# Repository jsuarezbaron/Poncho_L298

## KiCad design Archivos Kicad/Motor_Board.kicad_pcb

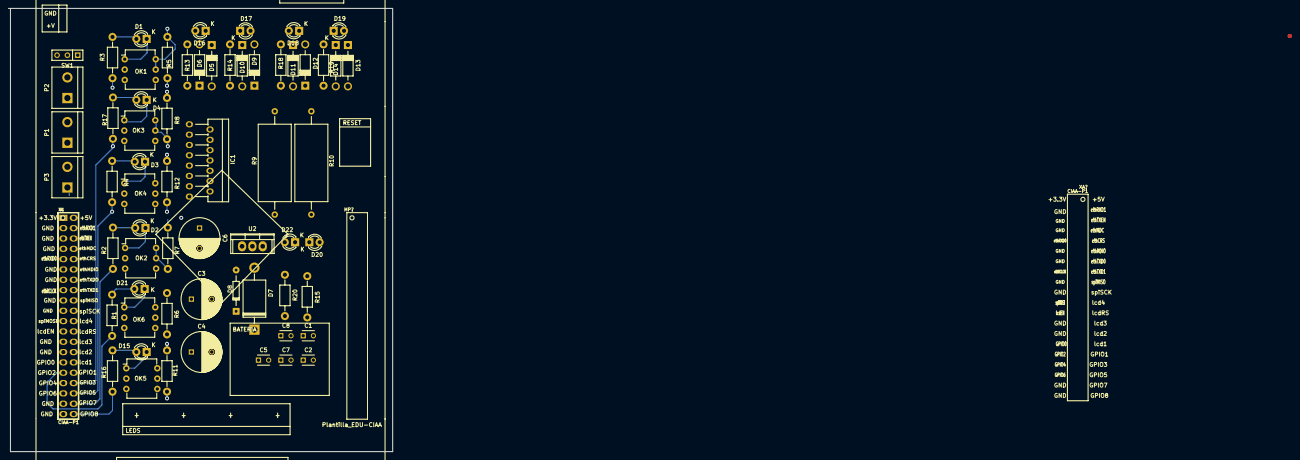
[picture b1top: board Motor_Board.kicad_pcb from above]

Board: 2 copper layers, 94.5 x 109.0 mm, 68 parts (0 on the bottom side), 34 nets.

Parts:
C1, C2, C5, C7, C8: 0.1uF; C_Disc_D3_P2.5
C3, C4: 470uF; C_Radial_D10_L25_P5
C6: 220uF; C_Radial_D10_L16_P5
D1, D2, D3, D4, D15, D16, D17, D18, D19, D20, D21, D22: Led_Small; LED-3MM
D5, D6, D9, D10, D11, D12, D13, D14: 1N4007; Diode_DO-41_SOD81_Horizontal_RM10
D7: 1N5822; Diode_DO-201AD_Horizontal_RM15
D8: 1N4734A; Diode_DO-35_SOD27_Horizontal_RM10
F1, F2, F3: FIDUCIAL; Fiducial_1mm
IC1: L298; Multiwatt_15_Vertical
MP?: Plantilla_EDU-CIAA
OK1, OK2, OK3, OK4, OK5, OK6: 4N35; DIP-6_W7.62mm
P1: Motor A; bornier2
P2: VDD Motor; bornier2
P3: Motor B; bornier2
R1, R2, R3, R4, R15, R16, R17: 330; Resistor_Horizontal_RM10mm
R5, R6, R7, R8, R11, R12, R13, R14, R18, R19, R20: 1K; Resistor_Horizontal_RM10mm
R9, R10: 0.5; Resistor_Ceramic_Horizontal_L19mm-W8mm-H8mm-p25mm
SW1: Switch_SPDT_x2; SW_Micro_SPST
U2: 7805; TO-220
XA1: Conn_Poncho2P_2x_20x2; Conn_Poncho_Izquierda
XA?: Plantilla_Poncho_Izquierda; Plantilla_Poncho_Plantilla_Poncho_Izquierda

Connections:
/ENA: IC1.6, OK6.5, OK6.6, R6.2
/ENB: IC1.11, OK5.5, OK5.6, R11.2
/IN1: IC1.5, OK1.5, OK1.6, R5.1
/IN2: IC1.7, OK2.5, OK2.6, R7.2
/IN3: IC1.10, OK3.5, OK3.6, R8.2
/IN4: IC1.12, OK4.5, OK4.6, R12.2
/OUT1: IC1.2, P1.1, R13.1
/OUT2: IC1.3, P1.2, R14.1
/OUT3: IC1.13, P3.1, R18.1
/OUT4: IC1.14, P3.2, R19.1
GNDA: C1.2, C2.2, C3.2, C4.2, C5.2, C6.2, C7.2, C8.2, D16.1, D17.1, D18.1, D19.1, D20.1, D20.2, D22.1, IC1.8, OK1.4, OK2.4, OK3.4, OK4.4, OK5.4, OK6.4, P2.1, R9.2, R10.2, R15.1
unnamed: D1.1, OK1.1
unnamed: D1.2, R3.1
unnamed: D2.1, OK2.1
unnamed: D2.2, R2.1
unnamed: D3.1, OK4.1
unnamed: D3.2, R4.1
unnamed: D4.1, OK3.1
unnamed: D4.2, R17.1
unnamed: D15.1, OK5.1
unnamed: D15.2, R16.1
unnamed: D16.2, R13.2
unnamed: D17.2, R14.2
unnamed: D18.2, R18.2
unnamed: D19.2, R19.2
unnamed: D21.1, OK6.1
unnamed: D21.2, R1.1
unnamed: D22.2, R20.1
unnamed: IC1.1, R9.1
unnamed: IC1.15, R10.1
unnamed: OK1.2, OK2.2, OK3.2, OK4.2, OK5.2, OK6.2
unnamed: P2.2, SW1.2
VCC: C2.1, C3.1, C4.1, C5.1, C8.1, IC1.4, R20.2
VDD: C1.1, C6.1, C7.1, IC1.9, R5.2, R6.1, R7.1, R8.1, R11.1, R12.1, R15.2

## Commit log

2016-07-28 Esquemático en PDF
2016-07-28 Documento descriptivo del proyecto.
2016-07-28 Hojas de datos utilizadas.
2016-07-28 Notas de ingeniería.
2016-07-28 Footprints
2016-07-28 Diseños de referencia.
2016-07-28 Archivos de kicad del proyecto.
2016-07-28 Modificaciones: Se eliminaron los HC04 y se habilitaron directamente las entradas (IN1, IN2, IN3, IN4). Las salidas de los motores se conectaron directamente al L298.
2016-07-28 Modificaciones en la asignación de tierras entre los optoacopladores y el conector de la Edu Ciaa. Nueva conexión de la tierra del led D19.
2016-07-30 Modificación de los capacitores de desacople del L298.
2016-08-01 Esquemático con los campos de digikey y mouser para hacer andar Kicost.
2016-08-24 Cambios realizados al esquemático y primeros pasos del PCB.
2016-08-24 Carpeta que contiene las huellas (footprints).
2016-08-28 Segunda versión del pcb. Ubicación de componentes de acuerdo a las medidas de la plantilla de la Edu Ciaa.
2016-08-31 Segunda versión del PCB.
